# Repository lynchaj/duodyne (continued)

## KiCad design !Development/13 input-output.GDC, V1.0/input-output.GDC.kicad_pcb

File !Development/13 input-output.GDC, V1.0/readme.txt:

This board provides a blank template for making input-output boards.  GAL information is notional and should be replaced with project specifics using Digital

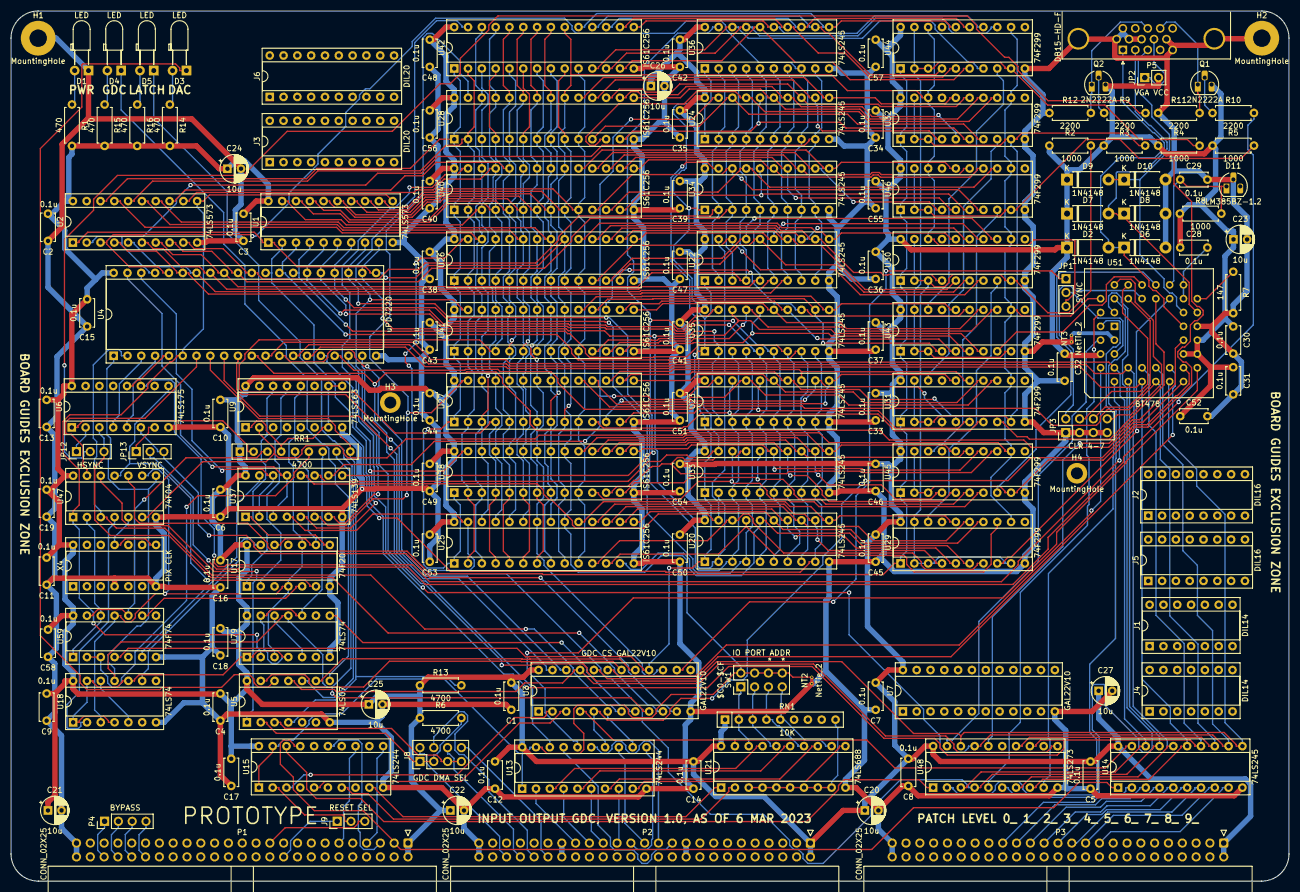
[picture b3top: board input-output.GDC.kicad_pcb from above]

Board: 2 copper layers, 235.0 x 160.0 mm, 159 parts (0 on the bottom side), 260 nets.

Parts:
C1, C2, C3, C4, C5, C6, C7, C8, C9, C10, C11, C12, C13, C14, C15, C16, C17, C18, C19, C28, C29, C30, C31, C32, C33, C34, C35, C36, C37, C38, C39, C40, C41, C42, C43, C44, C45, C46, C47, C48, C49, C50, C51, C52, C53, C54, C55, C56, C57, C58: 0.1u; C_Disc_D5.0mm_W2.5mm_P5.00mm
C20, C21, C22, C23, C24, C25, C26, C27: 10u; CP_Radial_D5.0mm_P2.50mm
D1, D3, D4, D5: LED; LED_D3.0mm_Horizontal_O3.81mm_Z2.0mm
D2, D6, D7, D8, D9, D10: 1N4148; D_DO-41_SOD81_P7.62mm_Horizontal
D11: LM385BZ-1.2; TO-92L_HandSolder
H1, H2: MountingHole; MountingHole_3.2mm_M3_Pad
H3, H4: MountingHole; MountingHole_2.2mm_M2_DIN965_Pad
J1, J4: DIL14; DIP-14_W7.62mm_Socket
J2, J5: DIL16; DIP-16_W7.62mm_Socket
J3, J6: DIL20; DIP-20_W7.62mm_Socket
J8: GDC DMA SEL; PinHeader_2x04_P2.54mm_Vertical
J9: RESET SEL; PinHeader_1x03_P2.54mm_Vertical
JP1: SYNC; PinHeader_1x03_P2.54mm_Vertical
JP2: VGA VCC; PinHeader_1x02_P2.54mm_Vertical
JP3: CLR 4-7; PinHeader_2x04_P2.54mm_Vertical
JP12: HSYNC; PinHeader_1x03_P2.54mm_Vertical
JP13: VSYNC; PinHeader_1x03_P2.54mm_Vertical
NT2, NT3: NetTie_2; NetTie-2_THT_Pad0.3mm
P1, P2, P3: CONN_02X25; IDC-Header_2x25_P2.54mm_Horizontal
P4: BYPASS; PinHeader_1x04_P2.54mm_Vertical
P5: DB15-HD-F; DSUB-15-HD_Female_Horizontal_P2.29x1.98mm_EdgePinOffset3.03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
Q1, Q2: 2N2222A; TO-92L_HandSolder
R1, R14, R15, R16: 470; R_Axial_DIN0207_L6.3mm_D2.5mm_P7.62mm_Horizontal
R2, R3, R4, R5, R8: 1000; R_Axial_DIN0207_L6.3mm_D2.5mm_P7.62mm_Horizontal
R6, R13: 4700; R_Axial_DIN0207_L6.3mm_D2.5mm_P7.62mm_Horizontal
R7: 147; R_Axial_DIN0207_L6.3mm_D2.5mm_P7.62mm_Horizontal
R9, R10, R11, R12: 2200; R_Axial_DIN0207_L6.3mm_D2.5mm_P7.62mm_Horizontal
RN1: 10K; R_Array_SIP9
RR1: 4700; R_Array_SIP9
SW1: IO PORT ADDR; PinHeader_2x04_P2.54mm_Vertical
U1, U2: 74LS573; DIP-20_W7.62mm_Socket
U3, U7: GAL22V10; DIP-24_W7.62mm_Socket
U4: uPD7220; DIP-40_W15.24mm_Socket
U5: 74LS07; DIP-14_W7.62mm_Socket
U6: 74LS175; DIP-16_W7.62mm_Socket
U9: 74LS163; DIP-16_W7.62mm_Socket
U13, U15: 74LS244; DIP-20_W7.62mm_Socket
U14, U20, U22, U23, U24, U33, U34, U35, U36: 74LS245; DIP-20_W7.62mm_Socket
U17: 74F20; DIP-14_W7.62mm_Socket
U18, U79: 74LS74; DIP-14_W7.62mm_Socket
U21: 74LS688; DIP-20_W7.62mm_Socket
U25, U26, U27, U28, U38, U40, U41, U42: IS61C256; DIP-28_W7.62mm_Socket
U29, U30, U31, U32, U43, U44, U45, U46: 74F299; DIP-20_W7.62mm_Socket
U37: 74LS139; DIP-16_W7.62mm_Socket
U47: 74F04; DIP-14_W7.62mm_Socket
U48: 74LS273; DIP-20_W7.62mm_Socket
U51: BT478; PLCC-44_THT-Socket
U59: 74F74; DIP-14_W7.62mm_Socket
X4: PIX CLK; DIP-14_W7.62mm_Socket

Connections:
2xWCLK: RR1.8 (R7), U3.9 (I8), U4.1 (2xWCLK), U18.11 (C), U47.8, U79.11 (C)
+12V: P2.19, P2.20
-12V: P2.37, P2.38
/RAMDAC/8-16: U48.19 (Q7), U51.2 (8/6)
/RAMDAC/BLU: D9.2 (A), D10.1 (K), P5.3, U51.27 (BLU)
/RAMDAC/GND_BT478: NT3.2, U51.3 (GND)
/RAMDAC/GRE: D7.2 (A), D8.1 (K), P5.2, U51.26 (GRE)
/RAMDAC/H-Sync: P5.13, Q2.1 (E), R12.2
/RAMDAC/OL0: U48.2 (Q0), U51.41 (OL0)
/RAMDAC/OL1: U48.5 (Q1), U51.42 (OL1)
/RAMDAC/OL2: U48.6 (Q2), U51.43 (OL2)
/RAMDAC/OL3: U48.9 (Q3), U51.44 (OL3)
/RAMDAC/RED: D2.2 (A), D6.1 (K), P5.1, U51.25 (RED)
/RAMDAC/SETUP: U48.16 (Q6), U51.23 (SET)
/RAMDAC/V-Sync: P5.14, Q1.1 (E), R11.2
/RAMDAC/VCC_VGA: JP2.1 (A), P5.9
/VSRAM/MA0: U1.12 (Q7), U25.10 (A0), U26.10 (A0), U27.10 (A0), U28.10 (A0), U38.10 (A0), U40.10 (A0), U41.10 (A0), U42.10 (A0)
/VSRAM/MA1: U1.13 (Q6), U25.9 (A1), U26.9 (A1), U27.9 (A1), U28.9 (A1), U38.9 (A1), U40.9 (A1), U41.9 (A1), U42.9 (A1)
/VSRAM/MA2: U1.14 (Q5), U25.8 (A2), U26.8 (A2), U27.8 (A2), U28.8 (A2), U38.8 (A2), U40.8 (A2), U41.8 (A2), U42.8 (A2)
/VSRAM/MA3: U1.15 (Q4), U25.7 (A3), U26.7 (A3), U27.7 (A3), U28.7 (A3), U38.7 (A3), U40.7 (A3), U41.7 (A3), U42.7 (A3)
/VSRAM/MA4: U1.16 (Q3), U25.6 (A4), U26.6 (A4), U27.6 (A4), U28.6 (A4), U38.6 (A4), U40.6 (A4), U41.6 (A4), U42.6 (A4)
/VSRAM/MA5: U1.17 (Q2), U25.5 (A5), U26.5 (A5), U27.5 (A5), U28.5 (A5), U38.5 (A5), U40.5 (A5), U41.5 (A5), U42.5 (A5)
/VSRAM/MA6: U1.18 (Q1), U25.4 (A6), U26.4 (A6), U27.4 (A6), U28.4 (A6), U38.4 (A6), U40.4 (A6), U41.4 (A6), U42.4 (A6)
/VSRAM/MA7: U1.19 (Q0), U25.3 (A7), U26.3 (A7), U27.3 (A7), U28.3 (A7), U38.3 (A7), U40.3 (A7), U41.3 (A7), U42.3 (A7)
/VSRAM/MA8: U2.12 (Q7), U25.25 (A8), U26.25 (A8), U27.25 (A8), U28.25 (A8), U38.25 (A8), U40.25 (A8), U41.25 (A8), U42.25 (A8)
/VSRAM/MA9: U2.13 (Q6), U25.24 (A9), U26.24 (A9), U27.24 (A9), U28.24 (A9), U38.24 (A9), U40.24 (A9), U41.24 (A9), U42.24 (A9)
/VSRAM/MA10: U2.14 (Q5), U25.21 (A10), U26.21 (A10), U27.21 (A10), U28.21 (A10), U38.21 (A10), U40.21 (A10), U41.21 (A10), U42.21 (A10)
/VSRAM/MA11: U2.15 (Q4), U25.23 (A11), U26.23 (A11), U27.23 (A11), U28.23 (A11), U38.23 (A11), U40.23 (A11), U41.23 (A11), U42.23 (A11)
/VSRAM/MA12: U2.16 (Q3), U25.2 (A12), U26.2 (A12), U27.2 (A12), U28.2 (A12), U38.2 (A12), U40.2 (A12), U41.2 (A12), U42.2 (A12)
/VSRAM/MA13: U2.17 (Q2), U25.26 (A13), U26.26 (A13), U27.26 (A13), U28.26 (A13), U38.26 (A13), U40.26 (A13), U41.26 (A13), U42.26 (A13)
/VSRAM/MA14: U2.18 (Q1), U25.1 (A14), U26.1 (A14), U27.1 (A14), U28.1 (A14), U38.1 (A14), U40.1 (A14), U41.1 (A14), U42.1 (A14)
/VSRAM/V0D0: U20.18 (B0), U25.11 (Q0), U29.7 (IO0)
/VSRAM/V0D1: U20.17 (B1), U25.12 (Q1), U29.13 (IO1)
/VSRAM/V0D2: U20.16 (B2), U25.13 (Q2), U29.6 (IO2)
/VSRAM/V0D3: U20.15 (B3), U25.15 (Q3), U29.14 (IO3)
/VSRAM/V0D4: U20.14 (B4), U25.16 (Q4), U29.5 (IO4)
/VSRAM/V0D5: U20.13 (B5), U25.17 (Q5), U29.15 (IO5)
/VSRAM/V0D6: U20.12 (B6), U25.18 (Q6), U29.4 (IO6)
/VSRAM/V0D7: U20.11 (B7), U25.19 (Q7), U29.16 (IO7)
/VSRAM/V0D8: U22.18 (B0), U26.11 (Q0), U30.7 (IO0)
/VSRAM/V0D9: U22.17 (B1), U26.12 (Q1), U30.13 (IO1)
/VSRAM/V0D10: U22.16 (B2), U26.13 (Q2), U30.6 (IO2)
/VSRAM/V0D11: U22.15 (B3), U26.15 (Q3), U30.14 (IO3)
/VSRAM/V0D12: U22.14 (B4), U26.16 (Q4), U30.5 (IO4)
/VSRAM/V0D13: U22.13 (B5), U26.17 (Q5), U30.15 (IO5)
/VSRAM/V0D14: U22.12 (B6), U26.18 (Q6), U30.4 (IO6)
/VSRAM/V0D15: U22.11 (B7), U26.19 (Q7), U30.16 (IO7)
/VSRAM/V1D0: U33.18 (B0), U38.11 (Q0), U45.7 (IO0)
/VSRAM/V1D1: U33.17 (B1), U38.12 (Q1), U45.13 (IO1)
/VSRAM/V1D2: U33.16 (B2), U38.13 (Q2), U45.6 (IO2)
/VSRAM/V1D3: U33.15 (B3), U38.15 (Q3), U45.14 (IO3)
/VSRAM/V1D4: U33.14 (B4), U38.16 (Q4), U45.5 (IO4)
/VSRAM/V1D5: U33.13 (B5), U38.17 (Q5), U45.15 (IO5)
/VSRAM/V1D6: U33.12 (B6), U38.18 (Q6), U45.4 (IO6)
/VSRAM/V1D7: U33.11 (B7), U38.19 (Q7), U45.16 (IO7)
/VSRAM/V1D8: U34.18 (B0), U40.11 (Q0), U46.7 (IO0)
/VSRAM/V1D9: U34.17 (B1), U40.12 (Q1), U46.13 (IO1)
/VSRAM/V1D10: U34.16 (B2), U40.13 (Q2), U46.6 (IO2)
/VSRAM/V1D11: U34.15 (B3), U40.15 (Q3), U46.14 (IO3)
/VSRAM/V1D12: U34.14 (B4), U40.16 (Q4), U46.5 (IO4)
/VSRAM/V1D13: U34.13 (B5), U40.17 (Q5), U46.15 (IO5)
/VSRAM/V1D14: U34.12 (B6), U40.18 (Q6), U46.4 (IO6)
/VSRAM/V1D15: U34.11 (B7), U40.19 (Q7), U46.16 (IO7)
/VSRAM/V2D0: U23.18 (B0), U27.11 (Q0), U31.7 (IO0)
/VSRAM/V2D1: U23.17 (B1), U27.12 (Q1), U31.13 (IO1)
/VSRAM/V2D2: U23.16 (B2), U27.13 (Q2), U31.6 (IO2)
/VSRAM/V2D3: U23.15 (B3), U27.15 (Q3), U31.14 (IO3)
/VSRAM/V2D4: U23.14 (B4), U27.16 (Q4), U31.5 (IO4)
/VSRAM/V2D5: U23.13 (B5), U27.17 (Q5), U31.15 (IO5)
/VSRAM/V2D6: U23.12 (B6), U27.18 (Q6), U31.4 (IO6)
/VSRAM/V2D7: U23.11 (B7), U27.19 (Q7), U31.16 (IO7)
/VSRAM/V2D8: U24.18 (B0), U28.11 (Q0), U32.7 (IO0)
/VSRAM/V2D9: U24.17 (B1), U28.12 (Q1), U32.13 (IO1)
/VSRAM/V2D10: U24.16 (B2), U28.13 (Q2), U32.6 (IO2)
/VSRAM/V2D11: U24.15 (B3), U28.15 (Q3), U32.14 (IO3)
/VSRAM/V2D12: U24.14 (B4), U28.16 (Q4), U32.5 (IO4)
/VSRAM/V2D13: U24.13 (B5), U28.17 (Q5), U32.15 (IO5)
/VSRAM/V2D14: U24.12 (B6), U28.18 (Q6), U32.4 (IO6)
/VSRAM/V2D15: U24.11 (B7), U28.19 (Q7), U32.16 (IO7)
/VSRAM/V3D0: U35.18 (B0), U41.11 (Q0), U43.7 (IO0)
/VSRAM/V3D1: U35.17 (B1), U41.12 (Q1), U43.13 (IO1)
/VSRAM/V3D2: U35.16 (B2), U41.13 (Q2), U43.6 (IO2)
/VSRAM/V3D3: U35.15 (B3), U41.15 (Q3), U43.14 (IO3)
/VSRAM/V3D4: U35.14 (B4), U41.16 (Q4), U43.5 (IO4)
/VSRAM/V3D5: U35.13 (B5), U41.17 (Q5), U43.15 (IO5)
/VSRAM/V3D6: U35.12 (B6), U41.18 (Q6), U43.4 (IO6)
/VSRAM/V3D7: U35.11 (B7), U41.19 (Q7), U43.16 (IO7)
/VSRAM/V3D8: U36.18 (B0), U42.11 (Q0), U44.7 (IO0)
/VSRAM/V3D9: U36.17 (B1), U42.12 (Q1), U44.13 (IO1)
/VSRAM/V3D10: U36.16 (B2), U42.13 (Q2), U44.6 (IO2)
/VSRAM/V3D11: U36.15 (B3), U42.15 (Q3), U44.14 (IO3)
/VSRAM/V3D12: U36.14 (B4), U42.16 (Q4), U44.5 (IO4)
/VSRAM/V3D13: U36.13 (B5), U42.17 (Q5), U44.15 (IO5)
/VSRAM/V3D14: U36.12 (B6), U42.18 (Q6), U44.4 (IO6)
/VSRAM/V3D15: U36.11 (B7), U42.19 (Q7), U44.16 (IO7)
/VSRAM/~DEBL0: U20.19 (CE), U22.19 (CE), U37.12 (O0)
/VSRAM/~DEBL1: U33.19 (CE), U34.19 (CE), U37.11 (O1)
/VSRAM/~DEBL2: U23.19 (CE), U24.19 (CE), U37.10 (O2)
/VSRAM/~DEBL3: U35.19 (CE), U36.19 (CE), U37.9 (O3)
/VSRAM/~WE0: U25.27 (~WE), U26.27 (~WE), U37.4 (O0)
/VSRAM/~WE1: U37.5 (O1), U38.27 (~WE), U40.27 (~WE)
/VSRAM/~WE2: U27.27 (~WE), U28.27 (~WE), U37.6 (O2)
/VSRAM/~WE3: U37.7 (O3), U41.27 (~WE), U42.27 (~WE)
/uPD7220/2xWCLK#: U9.12 (Q2), U17.4, U17.10, U18.3 (C), U47.9, U59.11 (C), U79.3 (C)
/uPD7220/ALE#: U47.2, U59.1 (~R), U59.12 (D)
/uPD7220/DBIN: U18.2 (D), U47.4
/uPD7220/DREQ#: U5.1, U47.12
/uPD7220/HSYNC+: JP12.1, U6.2 (Q0)
/uPD7220/PIX-CLK#: U47.5, X4.8, X4.11
/uPD7220/PU4.7K-H: RR1.2 (R1), U6.1 (~Mr)
/uPD7220/PU4.7K-I: RR1.3 (R2), U59.10 (~S), U59.13 (~R)
/uPD7220/PU4.7K-J: RR1.4 (R3), U9.1 (~MR), U9.7 (CEP), U9.9 (~PE), U9.10 (CET)
/uPD7220/PU4.7K-K: RR1.5 (R4), U17.9, U17.12
/uPD7220/PU4.7K-L: RR1.6 (R5), U59.2 (D), U59.3 (C)
/uPD7220/PU4.7K-M: RR1.7 (R6), U18.1 (~R), U18.4 (~S), U18.10 (~S), U18.13 (~R), U79.1 (~R), U79.4 (~S), U79.10 (~S), U79.13 (~R)
/uPD7220/TEND#: R13.2, RR1.9 (R8), U4.8 (/DACK), U5.4
/uPD7220/VSR-LD#: U6.9 (Cp), U17.6, U47.11
/uPD7220/VSYNC+: JP13.1, U6.7 (Q1)
A0: P2.35, U13.2 (I0a)
A1: P2.33, U13.4 (I1a)
A2: P2.31, U13.6 (I2a)
A3: P2.29, U13.8 (I3a)
A4: P2.27, U13.11 (I0b)
A5: P2.25, U13.13 (I1b)
A6: P2.23, U13.15 (I2b)
A7: P2.21, U13.17 (I3b)
AD0: U1.9 (D7), U4.22 (AD0), U20.2 (A0), U23.2 (A0), U33.2 (A0), U35.2 (A0)
AD1: U1.8 (D6), U4.23 (AD1), U20.3 (A1), U23.3 (A1), U33.3 (A1), U35.3 (A1)
AD2: U1.7 (D5), U4.24 (AD2), U20.4 (A2), U23.4 (A2), U33.4 (A2), U35.4 (A2)
AD3: U1.6 (D4), U4.25 (AD3), U20.5 (A3), U23.5 (A3), U33.5 (A3), U35.5 (A3)
AD4: U1.5 (D3), U4.26 (AD4), U20.6 (A4), U23.6 (A4), U33.6 (A4), U35.6 (A4)
AD5: U1.4 (D2), U4.27 (AD5), U20.7 (A5), U23.7 (A5), U33.7 (A5), U35.7 (A5)
AD6: U1.3 (D1), U4.28 (AD6), U20.8 (A6), U23.8 (A6), U33.8 (A6), U35.8 (A6)
AD7: U1.2 (D0), U4.29 (AD7), U20.9 (A7), U23.9 (A7), U33.9 (A7), U35.9 (A7)
AD8: U2.9 (D7), U4.30 (AD8), U22.2 (A0), U24.2 (A0), U34.2 (A0), U36.2 (A0)
AD9: U2.8 (D6), U4.31 (AD9), U22.3 (A1), U24.3 (A1), U34.3 (A1), U36.3 (A1)
AD10: U2.7 (D5), U4.32 (AD10), U22.4 (A2), U24.4 (A2), U34.4 (A2), U36.4 (A2)
AD11: U2.6 (D4), U4.33 (AD11), U22.5 (A3), U24.5 (A3), U34.5 (A3), U36.5 (A3)
AD12: U2.5 (D3), U4.34 (AD12), U22.6 (A4), U24.6 (A4), U34.6 (A4), U36.6 (A4)
AD13: U2.4 (D2), U4.35 (AD13), U22.7 (A5), U24.7 (A5), U34.7 (A5), U36.7 (A5)
AD14: U2.3 (D1), U4.36 (AD14), U22.8 (A6), U24.8 (A6), U34.8 (A6), U36.8 (A6)
AD15: U2.2 (D0), U4.37 (AD15), U22.9 (A7), U24.9 (A7), U34.9 (A7), U36.9 (A7)
AD16: U4.38 (A16), U37.2 (A0), U37.14 (A0)
AD17: U4.39 (A17), U37.3 (A1), U37.13 (A1)
ALE: U1.11 (Load), U2.11 (Load), U4.6 (ALE), U47.1, U79.2 (D)
COLOR0: U29.8 (Q0), U51.32 (P0)
COLOR1: U45.8 (Q0), U51.33 (P1)
COLOR2: U31.8 (Q0), U51.34 (P2)
COLOR3: U43.8 (Q0), U51.35 (P3)
COLOR4: JP3.2, U51.36 (P4)
COLOR5: JP3.4, U51.37 (P5)
COLOR6: JP3.6, U51.38 (P6)
COLOR7: JP3.8, U51.39 (P7)
D0: P3.33, U14.2 (A0)
D1: P3.31, U14.3 (A1)
D2: P3.29, U14.4 (A2)
D3: P3.27, U14.5 (A3)
D4: P3.25, U14.6 (A4)
D5: P3.23, U14.7 (A5)
D6: P3.21, U14.8 (A6)
D7: P3.19, U14.9 (A7)
GND: C1.2, C2.2, C3.2, C4.2, C5.2, C6.2, C7.2, C8.2, C9.2, C10.2, C11.2, C12.2, C13.2, C14.2, C15.2, C16.2, C17.2, C18.2, C19.2, C20.2, C21.2, C22.2, C23.2, C24.2, C25.2, C26.2, C27.2, C29.2, C30.2, C31.2, C32.2, C33.2, C34.2, C35.2, C36.2, C37.2, C38.2, C39.2, C40.2, C41.2, C42.2, C43.2, C44.2, C45.2, C46.2, C47.2, C48.2, C49.2, C50.2, C51.2, C52.2, C53.2, C54.2, C55.2, C56.2, C57.2, C58.2, D1.1 (K), D6.2 (A), D8.2 (A), D10.2 (A), D11.2 (A), H1.1, H2.1, JP3.1, JP3.3, JP3.5, JP3.7, NT2.1, NT3.1, P1.49, P1.50, P2.49, P2.50, P3.49, P3.50, P5.0, P5.5, P5.6, P5.7, P5.8, P5.10, P5.11, R7.2, R11.1, R12.1, U1.10 (GND), U2.10 (GND), U3.12 (GND), U4.20 (GND), U5.7 (GND), U6.8 (GND), U7.12 (GND), U9.8 (GND), U13.10 (GND), U14.10 (GND), U15.10 (GND), U17.7 (GND), U18.7 (GND), U20.10 (GND), U21.10 (GND), U22.10 (GND), U23.10 (GND), U24.10 (GND), U25.14 (GND), U26.14 (GND), U27.14 (GND), U28.14 (GND), U29.10 (GND), U30.10 (GND), U31.10 (GND), U32.10 (GND), U33.10 (GND), U34.10 (GND), U35.10 (GND), U36.10 (GND), U37.8 (GND), U38.14 (GND), U40.14 (GND), U41.14 (GND), U42.14 (GND), U43.10 (GND), U44.10 (GND), U45.10 (GND), U46.10 (GND), U47.7 (GND), U48.10 (GND), U51.24 (GND), U59.7 (GND), U79.7 (GND), X4.4, X4.7
H+VSYNC-: JP1.1, U3.14 (O9)
HSYNC-: JP12.3, U3.10 (I9), U6.3 (~Q0)
unnamed: C28.2, U51.29 (COMP), U51.30 (OPA)
unnamed: C29.1, D11.1 (K), R8.2, U51.31 (VREF)
unnamed: D1.2 (A), R1.1
unnamed: D3.1 (K), U5.12
unnamed: D3.2 (A), R14.1
unnamed: D4.1 (K), U5.8
unnamed: D4.2 (A), R15.1
unnamed: D5.1 (K), U5.10
unnamed: D5.2 (A), R16.1
unnamed: J8.1, J8.3, R6.2, U5.2
unnamed: J8.5, J8.7, U5.3
unnamed: J9.2, U15.2 (I0a)
unnamed: JP1.2, U51.5 (SYNC)
unnamed: Q1.2 (B), R10.1
unnamed: Q2.2 (B), R9.1
unnamed: R2.2, U29.2 (OE1), U29.3 (OE2), U29.9 (Mr), U29.19 (S1), U30.2 (OE1), U30.3 (OE2), U30.9 (Mr), U30.19 (S1)
unnamed: R3.2, U31.2 (OE1), U31.3 (OE2), U31.9 (Mr), U31.19 (S1), U32.2 (OE1), U32.3 (OE2), U32.9 (Mr), U32.19 (S1)
unnamed: R4.2, U43.2 (OE1), U43.3 (OE2), U43.9 (Mr), U43.19 (S1), U44.2 (OE1), U44.3 (OE2), U44.9 (Mr), U44.19 (S1)
unnamed: R5.2, U45.2 (OE1), U45.3 (OE2), U45.9 (Mr), U45.19 (S1), U46.2 (OE1), U46.3 (OE2), U46.9 (Mr), U46.19 (S1)
unnamed: R7.1, U51.28 (IREF)
unnamed: RN1.2 (R1), SW1.1, U21.18 (R7)
unnamed: RN1.3 (R2), SW1.3, U21.16 (R6)
unnamed: RN1.4 (R3), SW1.5, U21.14 (R5)
unnamed: RN1.5 (R4), SW1.7, U21.12 (R4)
unnamed: RN1.9 (R8), U21.3 (R0), U21.4 (P1), U21.5 (R1), U21.6 (P2), U21.7 (R2), U21.8 (P3), U21.9 (R3)
unnamed: U4.3 (HSYNC), U6.4 (D0)
unnamed: U4.4 (V/EXT_SYNC), U6.5 (D1)
unnamed: U4.5 (BLANK), U6.12 (D2)
unnamed: U4.7 (DRQ), U47.13
unnamed: U9.14 (Q0), U17.1
unnamed: U9.13 (Q1), U17.2
unnamed: U17.5, U59.9 (Q)
unnamed: U17.13, U18.9 (Q)
unnamed: U18.5 (Q), U18.12 (D)
unnamed: U29.18 (Ds7), U30.8 (Q0)
unnamed: U31.18 (Ds7), U32.8 (Q0)
unnamed: U43.18 (Ds7), U44.8 (Q0)
unnamed: U45.18 (Ds7), U46.8 (Q0)
unnamed: U79.5 (Q), U79.12 (D)
PIX-CLK: U9.2 (CP), U29.12 (Cp), U30.12 (Cp), U31.12 (Cp), U32.12 (Cp), U43.12 (Cp), U44.12 (Cp), U45.12 (Cp), U46.12 (Cp), U47.6, U51.40 (PCLK)
VCC: C1.1, C2.1, C3.1, C4.1, C5.1, C6.1, C7.1, C8.1, C9.1, C10.1, C11.1, C12.1, C13.1, C14.1, C15.1, C16.1, C17.1, C18.1, C19.1, C20.1, C21.1, C22.1, C23.1, C24.1, C25.1, C26.1, C27.1, C28.1, C30.1, C31.1, C32.1, C33.1, C34.1, C35.1, C36.1, C37.1, C38.1, C39.1, C40.1, C41.1, C42.1, C43.1, C44.1, C45.1, C46.1, C47.1, C48.1, C49.1, C50.1, C51.1, C52.1, C53.1, C54.1, C55.1, C56.1, C57.1, C58.1, D2.1 (K), D7.1 (K), D9.1 (K), JP2.2 (B), P1.1, P1.2, P2.1, P2.2, P3.1, P3.2, Q1.3 (C), Q2.3 (C), R1.2, R2.1, R3.1, R4.1, R5.1, R6.1, R8.1, R13.1, R14.2, R15.2, R16.2, RN1.1 (common), RR1.1 (common), U1.20 (VCC), U2.20 (VCC), U3.24 (VCC), U4.40 (VCC), U5.14 (VCC), U6.16 (VCC), U7.24 (VCC), U9.16 (VCC), U13.20 (VCC), U14.20 (VCC), U15.20 (VCC), U17.14 (VCC), U18.14 (VCC), U20.20 (VCC), U21.20 (VCC), U22.20 (VCC), U23.20 (VCC), U24.20 (VCC), U25.28 (VCC), U26.28 (VCC), U27.28 (VCC), U28.28 (VCC), U29.20 (VCC), U30.20 (VCC), U31.20 (VCC), U32.20 (VCC), U33.20 (VCC), U34.20 (VCC), U35.20 (VCC), U36.20 (VCC), U37.16 (VCC), U38.28 (VCC), U40.28 (VCC), U41.28 (VCC), U42.28 (VCC), U43.20 (VCC), U44.20 (VCC), U45.20 (VCC), U46.20 (VCC), U47.14 (VCC), U48.20 (VCC), U51.4 (VAA), U51.20 (VAA), U51.21 (VAA), U51.22 (VAA), U59.14 (VCC), U79.14 (VCC), X4.14
VSR-LD: U29.1 (S0), U30.1 (S0), U31.1 (S0), U32.1 (S0), U43.1 (S0), U44.1 (S0), U45.1 (S0), U46.1 (S0), U47.10
VSYNC-: JP13.3, U3.11 (I10), U6.6 (~Q1)
ZERO: JP1.3, NT2.2, SW1.2, SW1.4, SW1.6, SW1.8, U1.1 (OE), U2.1 (OE), U4.21 (LPEN/DH), U13.1 (OEa), U13.19 (OEb), U15.1 (OEa), U15.19 (OEb), U25.20 (~CS), U26.20 (~CS), U27.20 (~CS), U28.20 (~CS), U30.18 (Ds7), U32.18 (Ds7), U38.20 (~CS), U40.20 (~CS), U41.20 (~CS), U42.20 (~CS), U44.18 (Ds7), U46.18 (Ds7)
bA0: U4.11 (A0), U13.18 (O0a), U51.17 (RS0)
bA1: U13.16 (O1a), U51.18 (RS1)
bA2: U3.5 (I4), U13.14 (O2a), U51.19 (RS2)
bA3: U3.6 (I5), U13.12 (O3a)
bA4: U13.9 (O0b), U21.11 (P4)
bA5: U13.7 (O1b), U21.13 (P5)
bA6: U13.5 (O2b), U21.15 (P6)
bA7: U13.3 (O3b), U21.17 (P7)
bD0: U4.12 (DB0), U14.18 (B0), U48.3 (D0), U51.8 (D0)
bD1: U4.13 (DB1), U14.17 (B1), U48.4 (D1), U51.9 (D1)
bD2: U4.14 (DB2), U14.16 (B2), U48.7 (D2), U51.10 (D2)
bD3: U4.15 (DB3), U14.15 (B3), U48.8 (D3), U51.11 (D3)
bD4: U4.16 (DB4), U14.14 (B4), U48.13 (D4), U51.12 (D4)
bD5: U4.17 (DB5), U14.13 (B5), U48.14 (D5), U51.13 (D5)
bD6: U4.18 (DB6), U14.12 (B6), U48.17 (D6), U51.14 (D6)
bD7: U4.19 (DB7), U14.11 (B7), U48.18 (D7), U51.15 (D7)
~ALE2: U3.8 (I7), U79.8 (~Q)
~BAI: P1.40, P4.4
~BAO: P1.42, P4.3
~BLANK: U6.11 (~Q2), U51.7 (BLANK)
~CS_BRD: U3.4 (I3), U14.19 (CE), U21.19 (P=R)
~CS_GDC_RD: U3.23 (O0), U4.9 (/RD)
~CS_GDC_WR: U3.22 (O1), U4.10 (/WR)
~CS_GDC: U3.17 (O6), U5.9
~CS_LATCH: U3.21 (O2), U5.11, U48.11 (Cp)
~CS_RAMDAC_RD: U3.19 (O4), U51.6 (RD)
~CS_RAMDAC_WR: U3.20 (O3), U51.16 (WR)
~CS_RAMDAC: U3.18 (O5), U5.13
~DBIN_GDC: U3.7 (I6), U4.2 (/DBIN), U47.3
~DBIN: U3.16 (O7), U20.1 (A->B), U22.1 (A->B), U23.1 (A->B), U24.1 (A->B), U33.1 (A->B), U34.1 (A->B), U35.1 (A->B), U36.1 (A->B), U59.4 (~S)
~DEBL: U37.15 (E), U59.6 (~Q)
~DREQ0: J8.2, P2.46
~DREQ1: J8.4, P2.42
~HSYNC: JP12.2, R9.2
~IEI: P1.44, P4.2
~IEO: P1.46, P4.1
~IORQ: P1.7, U15.11 (I0b)
~M1: P1.11, U15.13 (I1b)
~RD: P1.3, U14.1 (A->B), U15.17 (I3b)
~READ_VRAM: U3.15 (O8), U25.22 (~OE), U26.22 (~OE), U27.22 (~OE), U28.22 (~OE), U38.22 (~OE), U40.22 (~OE), U41.22 (~OE), U42.22 (~OE)
~RES_IN: J9.1, P1.20
~RES_OUT: J9.3, P1.21
~TEND0: J8.6, P2.44
~TEND1: J8.8, P2.40
~VSYNC: JP13.2, R10.2
~WE: U17.8, U37.1 (E)
~WR: P1.5, U15.15 (I2b)
~bIORQ: U15.9 (O0b), U21.1 (G)
~bM1: U15.7 (O1b), U21.2 (P0)
~bRD: U3.2 (I1), U15.3 (O3b)
~bRESET: U15.18 (O0a), U48.1 (~Mr)
~bWR: U3.3 (I2), U15.5 (O2b)

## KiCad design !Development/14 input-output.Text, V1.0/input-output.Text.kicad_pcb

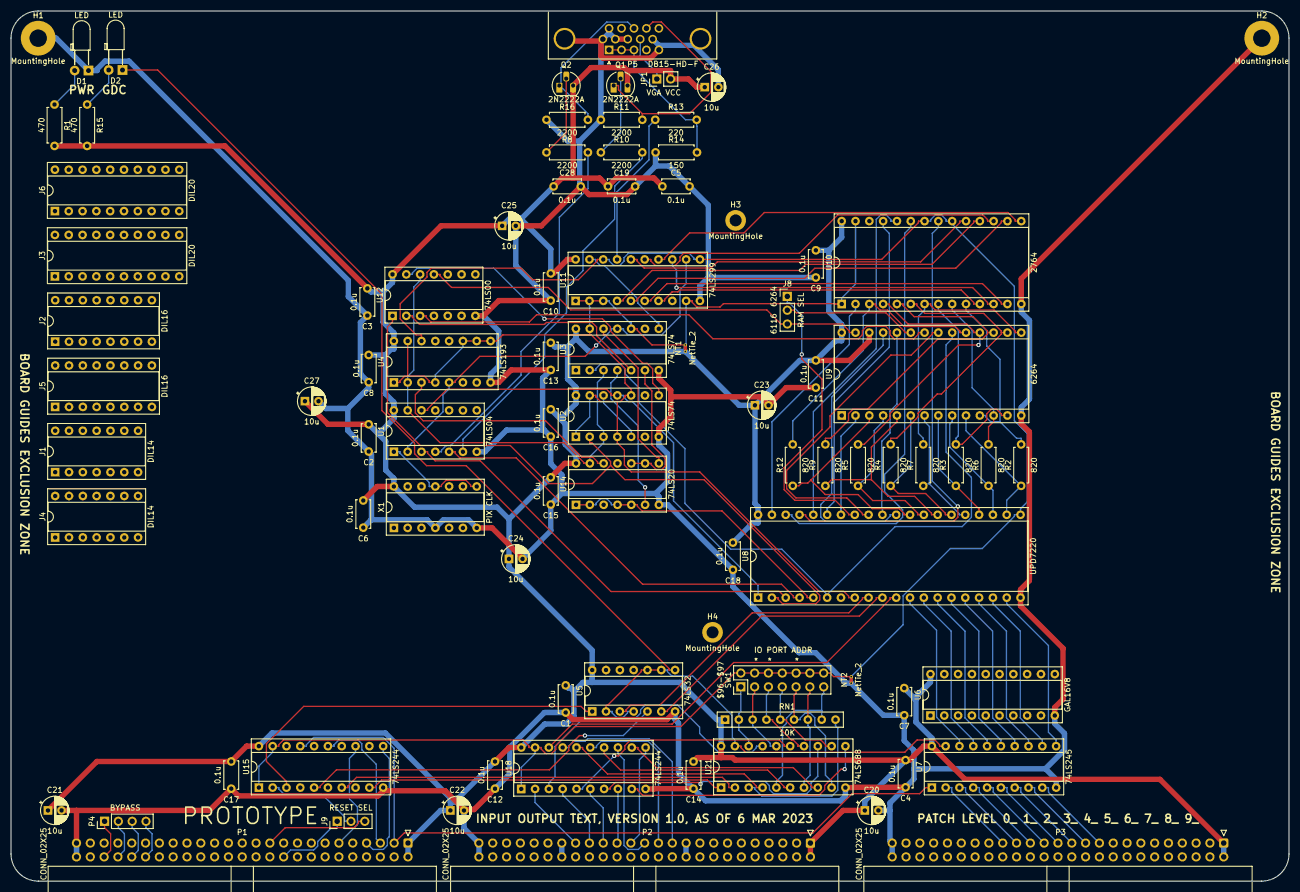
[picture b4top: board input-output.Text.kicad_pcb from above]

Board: 2 copper layers, 235.0 x 160.0 mm, 87 parts (0 on the bottom side), 130 nets.

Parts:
C1, C2, C3, C4, C5, C6, C7, C8, C9, C10, C11, C12, C13, C14, C15, C16, C17, C18, C19, C28: 0.1u; C_Disc_D5.0mm_W2.5mm_P5.00mm
C20, C21, C22, C23, C24, C25, C26, C27: 10u; CP_Radial_D5.0mm_P2.50mm
D1, D2: LED; LED_D3.0mm_Horizontal_O3.81mm_Z2.0mm
H1, H2: MountingHole; MountingHole_3.2mm_M3_Pad
H3, H4: MountingHole; MountingHole_2.2mm_M2_DIN965_Pad
J1, J4: DIL14; DIP-14_W7.62mm_Socket
J2, J5: DIL16; DIP-16_W7.62mm_Socket
J3, J6: DIL20; DIP-20_W7.62mm_Socket
J8: RAM SEL; PinHeader_1x03_P2.54mm_Vertical
J9: RESET SEL; PinHeader_1x03_P2.54mm_Vertical
JP1: VGA VCC; PinHeader_1x02_P2.54mm_Vertical
NT1, NT2: NetTie_2; NetTie-2_THT_Pad0.3mm
P1, P2, P3: CONN_02X25; IDC-Header_2x25_P2.54mm_Horizontal
P4: BYPASS; PinHeader_1x04_P2.54mm_Vertical
P5: DB15-HD-F; DSUB-15-HD_Female_Horizontal_P2.29x1.98mm_EdgePinOffset3.03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
Q1, Q2: 2N2222A; TO-92L_HandSolder
R1, R15: 470; R_Axial_DIN0207_L6.3mm_D2.5mm_P7.62mm_Horizontal
R2, R3, R4, R5, R6, R7, R9, R12: 820; R_Axial_DIN0207_L6.3mm_D2.5mm_P7.62mm_Horizontal
R8, R10, R11, R16: 2200; R_Axial_DIN0207_L6.3mm_D2.5mm_P7.62mm_Horizontal
R13: 220; R_Axial_DIN0207_L6.3mm_D2.5mm_P7.62mm_Horizontal
R14: 150; R_Axial_DIN0207_L6.3mm_D2.5mm_P7.62mm_Horizontal
RN1: 10K; R_Array_SIP9
SW1: IO PORT ADDR; PinHeader_2x07_P2.54mm_Vertical
U1: 74LS04; DIP-14_W7.62mm_Socket
U2, U3: 74LS74; DIP-14_W7.62mm_Socket
U4: 74LS193; DIP-16_W7.62mm_Socket
U5: 74LS32; DIP-14_W7.62mm_Socket
U6: GAL16V8; DIP-20_W7.62mm_Socket
U7: 74LS245; DIP-20_W7.62mm_Socket
U8: UPD7220; DIP-40_W15.24mm_Socket
U9: 6264; DIP-28_W15.24mm_Socket
U10: 2764; DIP-28_W15.24mm_Socket
U11: 74LS299; DIP-20_W7.62mm_Socket
U12: 74LS00; DIP-14_W7.62mm_Socket
U14: 74LS20; DIP-14_W7.62mm_Socket
U15, U18: 74LS244; DIP-20_W7.62mm_Socket
U21: 74LS688; DIP-20_W7.62mm_Socket
X1: PIX CLK; DIP-14_W7.62mm_Socket

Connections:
+12V: P2.19, P2.20
-12V: P2.37, P2.38
/GDC-Text/2xWCLK: U1.12, U2.11 (C), U8.1 (2xWCLK)
/GDC-Text/A16: U8.38 (A16), U10.23 (A11)
/GDC-Text/A17: U8.39 (A17), U10.2 (A12)
/GDC-Text/AD0: R2.1, U8.22 (AD0), U9.10 (A0)
/GDC-Text/AD1: R6.1, U8.23 (AD1), U9.9 (A1)
/GDC-Text/AD2: R3.1, U8.24 (AD2), U9.8 (A2)
/GDC-Text/AD3: R7.1, U8.25 (AD3), U9.7 (A3)
/GDC-Text/AD4: R4.1, U8.26 (AD4), U9.6 (A4)
/GDC-Text/AD5: R9.1, U8.27 (AD5), U9.5 (A5)
/GDC-Text/AD6: R5.1, U8.28 (AD6), U9.4 (A6)
/GDC-Text/AD7: R12.1, U8.29 (AD7), U9.3 (A7)
/GDC-Text/AD8: U8.30 (AD8), U9.25 (A8)
/GDC-Text/AD9: U8.31 (AD9), U9.24 (A9)
/GDC-Text/AD10: U8.32 (AD10), U9.21 (A10)
/GDC-Text/AD11: J8.1, U8.33 (AD11)
/GDC-Text/AD12: U8.34 (AD12), U9.2 (A12)
/GDC-Text/AD13: U8.35 (AD13), U10.25 (A8)
/GDC-Text/AD14: U8.36 (AD14), U10.24 (A9)
/GDC-Text/AD15: U8.37 (AD15), U10.21 (A10)
/GDC-Text/ALE: U3.2 (D), U8.6 (ALE), U9.20 (~CS1)
/GDC-Text/BLANK: U8.5 (BLANK), U14.1, U14.2, U14.4, U14.5
/GDC-Text/CD0: U10.11 (D0), U11.7 (IO0)
/GDC-Text/CD1: U10.12 (D1), U11.13 (IO1)
/GDC-Text/CD2: U10.13 (D2), U11.6 (IO2)
/GDC-Text/CD3: U10.15 (D3), U11.14 (IO3)
/GDC-Text/CD4: U10.16 (D4), U11.5 (IO4)
/GDC-Text/CD5: U10.17 (D5), U11.15 (IO5)
/GDC-Text/CD6: U10.18 (D6), U11.4 (IO6)
/GDC-Text/CD7: U10.19 (D7), U11.16 (IO7)
/GDC-Text/H-Sync: P5.13, Q2.1 (E), R16.2
/GDC-Text/HSYNC: U1.3, U8.3 (HSYNC)
/GDC-Text/MD0: R2.2, U9.11 (Q0), U10.10 (A0)
/GDC-Text/MD1: R6.2, U9.12 (Q1), U10.9 (A1)
/GDC-Text/MD2: R3.2, U9.13 (Q2), U10.8 (A2)
/GDC-Text/MD3: R7.2, U9.15 (Q3), U10.7 (A3)
/GDC-Text/MD4: R4.2, U9.16 (Q4), U10.6 (A4)
/GDC-Text/MD5: R9.2, U9.17 (Q5), U10.5 (A5)
/GDC-Text/MD6: R5.2, U9.18 (Q6), U10.4 (A6)
/GDC-Text/MD7: R12.2, U9.19 (Q7), U10.3 (A7)
/GDC-Text/PIX-CLK: U1.2, U3.11 (C), U4.5 (UP), U11.12 (Cp)
/GDC-Text/V-Sync: P5.14, Q1.1 (E), R11.2
/GDC-Text/VCC_VGA: JP1.1 (A), P5.9
/GDC-Text/VGA_TTL: R13.1, U11.17 (Q7)
/GDC-Text/VSYNC: U1.5, U8.4 (V/EXT_SYNC)
/GDC-Text/~2xWCLK: U1.13, U2.3 (C), U3.3 (C), U4.2 (QB), U12.12, U14.13
/GDC-Text/~BLANK: U3.4 (~S), U14.6
/GDC-Text/~DBIN: U2.2 (D), U8.2 (/DBIN), U12.1
/GDC-Text/~OE_RAM: U9.22 (~OE), U12.3
/GDC-Text/~PIX-CLK: U1.1, X1.8, X1.11
/GDC-Text/~WE_RAM: J8.3, U9.27 (~WE), U12.11
A0: P2.35, U18.2 (I0a)
A1: P2.33, U18.4 (I1a)
A2: P2.31, U18.6 (I2a)
A3: P2.29, U18.8 (I3a)
A4: P2.27, U18.11 (I0b)
A5: P2.25, U18.13 (I1b)
A6: P2.23, U18.15 (I2b)
A7: P2.21, U18.17 (I3b)
D0: P3.33, U7.2 (A0)
D1: P3.31, U7.3 (A1)
D2: P3.29, U7.4 (A2)
D3: P3.27, U7.5 (A3)
D4: P3.25, U7.6 (A4)
D5: P3.23, U7.7 (A5)
D6: P3.21, U7.8 (A6)
D7: P3.19, U7.9 (A7)
GND: C1.2, C2.2, C3.2, C4.2, C5.2, C6.2, C7.2, C8.2, C9.2, C10.2, C11.2, C12.2, C13.2, C14.2, C15.2, C16.2, C17.2, C18.2, C19.2, C20.2, C21.2, C22.2, C23.2, C24.2, C25.2, C26.2, C27.2, C28.2, D1.1 (K), H1.1, H2.1, NT2.1, P1.49, P1.50, P2.49, P2.50, P3.49, P3.50, P5.0, P5.5, P5.6, P5.7, P5.8, P5.10, P5.11, R11.1, R14.1, R16.1, U1.7 (GND), U2.7 (GND), U3.7 (GND), U4.8 (GND), U5.7 (GND), U6.10 (GND), U7.10 (GND), U8.20 (GND), U9.14 (GND), U10.14 (GND), U11.10 (GND), U12.7 (GND), U14.7 (GND), U15.10 (GND), U18.10 (GND), U21.10 (GND), X1.4, X1.7
unnamed: D1.2 (A), R1.1
unnamed: D2.1 (K), U5.8
unnamed: D2.2 (A), R15.1
unnamed: J8.2, U9.23 (A11)
unnamed: J9.2, U15.2 (I0a)
unnamed: P5.1, P5.2, P5.3, R13.2, R14.2
unnamed: Q1.2 (B), R10.1
unnamed: Q2.2 (B), R8.1
unnamed: R8.2, U1.4
unnamed: R10.2, U1.6
unnamed: RN1.2 (R1), SW1.1, U21.18 (R7)
unnamed: RN1.3 (R2), SW1.3, U21.16 (R6)
unnamed: RN1.4 (R3), SW1.5, U21.14 (R5)
unnamed: RN1.5 (R4), SW1.7, U21.12 (R4)
unnamed: RN1.6 (R5), SW1.9, U21.9 (R3)
unnamed: RN1.7 (R6), SW1.11, U21.7 (R2)
unnamed: RN1.8 (R7), SW1.13, U21.5 (R1)
unnamed: RN1.9 (R8), U21.3 (R0)
unnamed: U2.5 (Q), U2.12 (D)
unnamed: U3.8 (~Q), U11.19 (S1)
unnamed: U3.5 (Q), U12.2
unnamed: U2.8 (~Q), U12.13
unnamed: U3.12 (D), U14.8
unnamed: U3.6 (~Q), U14.9, U14.10
unnamed: U4.3 (QA), U14.12
ONE: NT1.2, U2.1 (~R), U2.4 (~S), U2.10 (~S), U2.13 (~R), U3.10 (~S), U3.13 (~R), U4.1 (B), U4.4 (DOWN), U4.9 (D), U4.10 (C), U4.11 (~LOAD), U4.15 (A), U8.8 (/DACK), U10.1 (VPP), U10.27 (~PGM), U11.1 (S0), U11.2 (OE1), U11.3 (OE2), U11.9 (Mr)
VCC: C1.1, C2.1, C3.1, C4.1, C5.1, C6.1, C7.1, C8.1, C9.1, C10.1, C11.1, C12.1, C13.1, C14.1, C15.1, C16.1, C17.1, C18.1, C19.1, C20.1, C21.1, C22.1, C23.1, C24.1, C25.1, C26.1, C27.1, C28.1, JP1.2 (B), NT1.1, P1.1, P1.2, P2.1, P2.2, P3.1, P3.2, Q1.3 (C), Q2.3 (C), R1.2, R15.2, RN1.1 (common), U1.14 (VCC), U2.14 (VCC), U3.14 (VCC), U4.16 (VCC), U5.14 (VCC), U6.20 (VCC), U7.20 (VCC), U8.40 (VCC), U9.26 (CS2), U9.28 (VCC), U10.28 (VCC), U11.20 (VCC), U12.14 (VCC), U14.14 (VCC), U15.20 (VCC), U18.20 (VCC), U21.20 (VCC), X1.14
ZERO: NT2.2, SW1.2, SW1.4, SW1.6, SW1.8, SW1.10, SW1.12, SW1.14, U4.14 (CLR), U8.21 (LPEN/DH), U10.20 (~CE), U10.22 (~OE), U11.11 (Ds0), U11.18 (Ds7), U15.1 (OEa), U15.19 (OEb), U18.1 (OEa), U18.19 (OEb)
bA0: U8.11 (A0), U18.18 (O0a)
bA1: U18.16 (O1a), U21.4 (P1)
bA2: U18.14 (O2a), U21.6 (P2)
bA3: U18.12 (O3a), U21.8 (P3)
bA4: U18.9 (O0b), U21.11 (P4)
bA5: U18.7 (O1b), U21.13 (P5)
bA6: U18.5 (O2b), U21.15 (P6)
bA7: U18.3 (O3b), U21.17 (P7)
bD0: U7.18 (B0), U8.12 (DB0)
bD1: U7.17 (B1), U8.13 (DB1)
bD2: U7.16 (B2), U8.14 (DB2)
bD3: U7.15 (B3), U8.15 (DB3)
bD4: U7.14 (B4), U8.16 (DB4)
bD5: U7.13 (B5), U8.17 (DB5)
bD6: U7.12 (B6), U8.18 (DB6)
bD7: U7.11 (B7), U8.19 (DB7)
~BAI: P1.40, P4.4
~BAO: P1.42, P4.3
~CS_TEXT_RD: U5.3, U8.9 (/RD)
~CS_TEXT_WR: U5.6, U8.10 (/WR)
~CS_TEXT: U5.2, U5.4, U5.9, U5.10, U7.19 (CE), U21.19 (P=R)
~IEI: P1.44, P4.2
~IEO: P1.46, P4.1
~IORQ: P1.7, U15.11 (I0b)
~M1: P1.11, U15.13 (I1b)
~RD: P1.3, U7.1 (A->B), U15.17 (I3b)
~RES_IN: J9.1, P1.20
~RES_OUT: J9.3, P1.21
~WR: P1.5, U15.15 (I2b)
~bIORQ: U15.9 (O0b), U21.1 (G)
~bM1: U15.7 (O1b), U21.2 (P0)
~bRD: U5.1, U15.3 (O3b)
~bWR: U5.5, U15.5 (O2b)
